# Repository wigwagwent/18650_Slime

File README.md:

# slimevr_pcb
A PCB design the size of a 18650 battery that supports the BMI160 designed for SlimeVR full-body trackers

- [18650_Slime-Main](/hardware/18650_Slime_main/) - A fully custom PCB that handles the IMU.

  Unlike most of the SlimeVR community, it uses the ESP32-C3, a newer and more
  powerful chip. Designed to be a more powerful development platform, as it natively
  supports JTAG debugging over USB, more compilers and languages, including Rust,
  and supports Bluetooth LE v5.0.

- [18650_Slime-Battery](/hardware/18650_Slime_battery/) - Combines fast charging with protection

  It can be used with other boards that want an 18650 cell with a built in charge controller.

## License
**This hardware is licensed under the CERN-OHL-P v2 license**, which is a permissive,
non-viral and non-reciprocal open hardware license. Unlike software licenses like
MIT and Apache 2.0, it better handles the nuances of hardware and protects both
the licensor and licensee from patent lawsuits.

**Unless you explicitly state otherwise, any contribution intentionally submitted
for inclusion in this work by you, shall be licensed as above, without any
additional terms or conditions.**

### Conveying notice of License
Note that as part of the CERN-OHL-P v2 license, recipients of manufactured
hardware must also receive notice of the above license. One such
method of conveying the notice is to include a link to the original source repo,
or printing "Licensed under CERN-OHL-P v2" on the PCB silkscreen. For more info,
see [here](https://ohwr.org/project/cernohl/wikis/uploads/8a6b5d01f71c207c49493e4d114d61e6/cern_ohl_p_v2_howto.pdf).

This is conceptually similar to the MIT/Apache 2.0 Licenses, where the original
license must still be included as a notice even when the source is modified and
subsequently relicensed under different terms.

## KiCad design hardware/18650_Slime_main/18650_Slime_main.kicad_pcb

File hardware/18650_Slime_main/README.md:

# 18650 SlimeVR
This PCB is designed to be about the same size as a 18650 cell once fully assembled
and stacked. This is a stacked board design but in theory, all the hardware should
be able to fit onto one board but is separated to two boards.

## Useful Information
- IMU: BMI160 Module
- ESP32-C3 main processor

## Renders

## Changelog
A description of the changes in each revision can be found [here](CHANGELOG.md).

## Credits
The schematic was based on version 3.0 of the .
Big thanks to TheButlah for all the work he put into this schematic and into slimevr.
Also big thanks to Mosaic-Industries for there push button 
Final thanks to this github project that implements a usefull  for jlcpcb

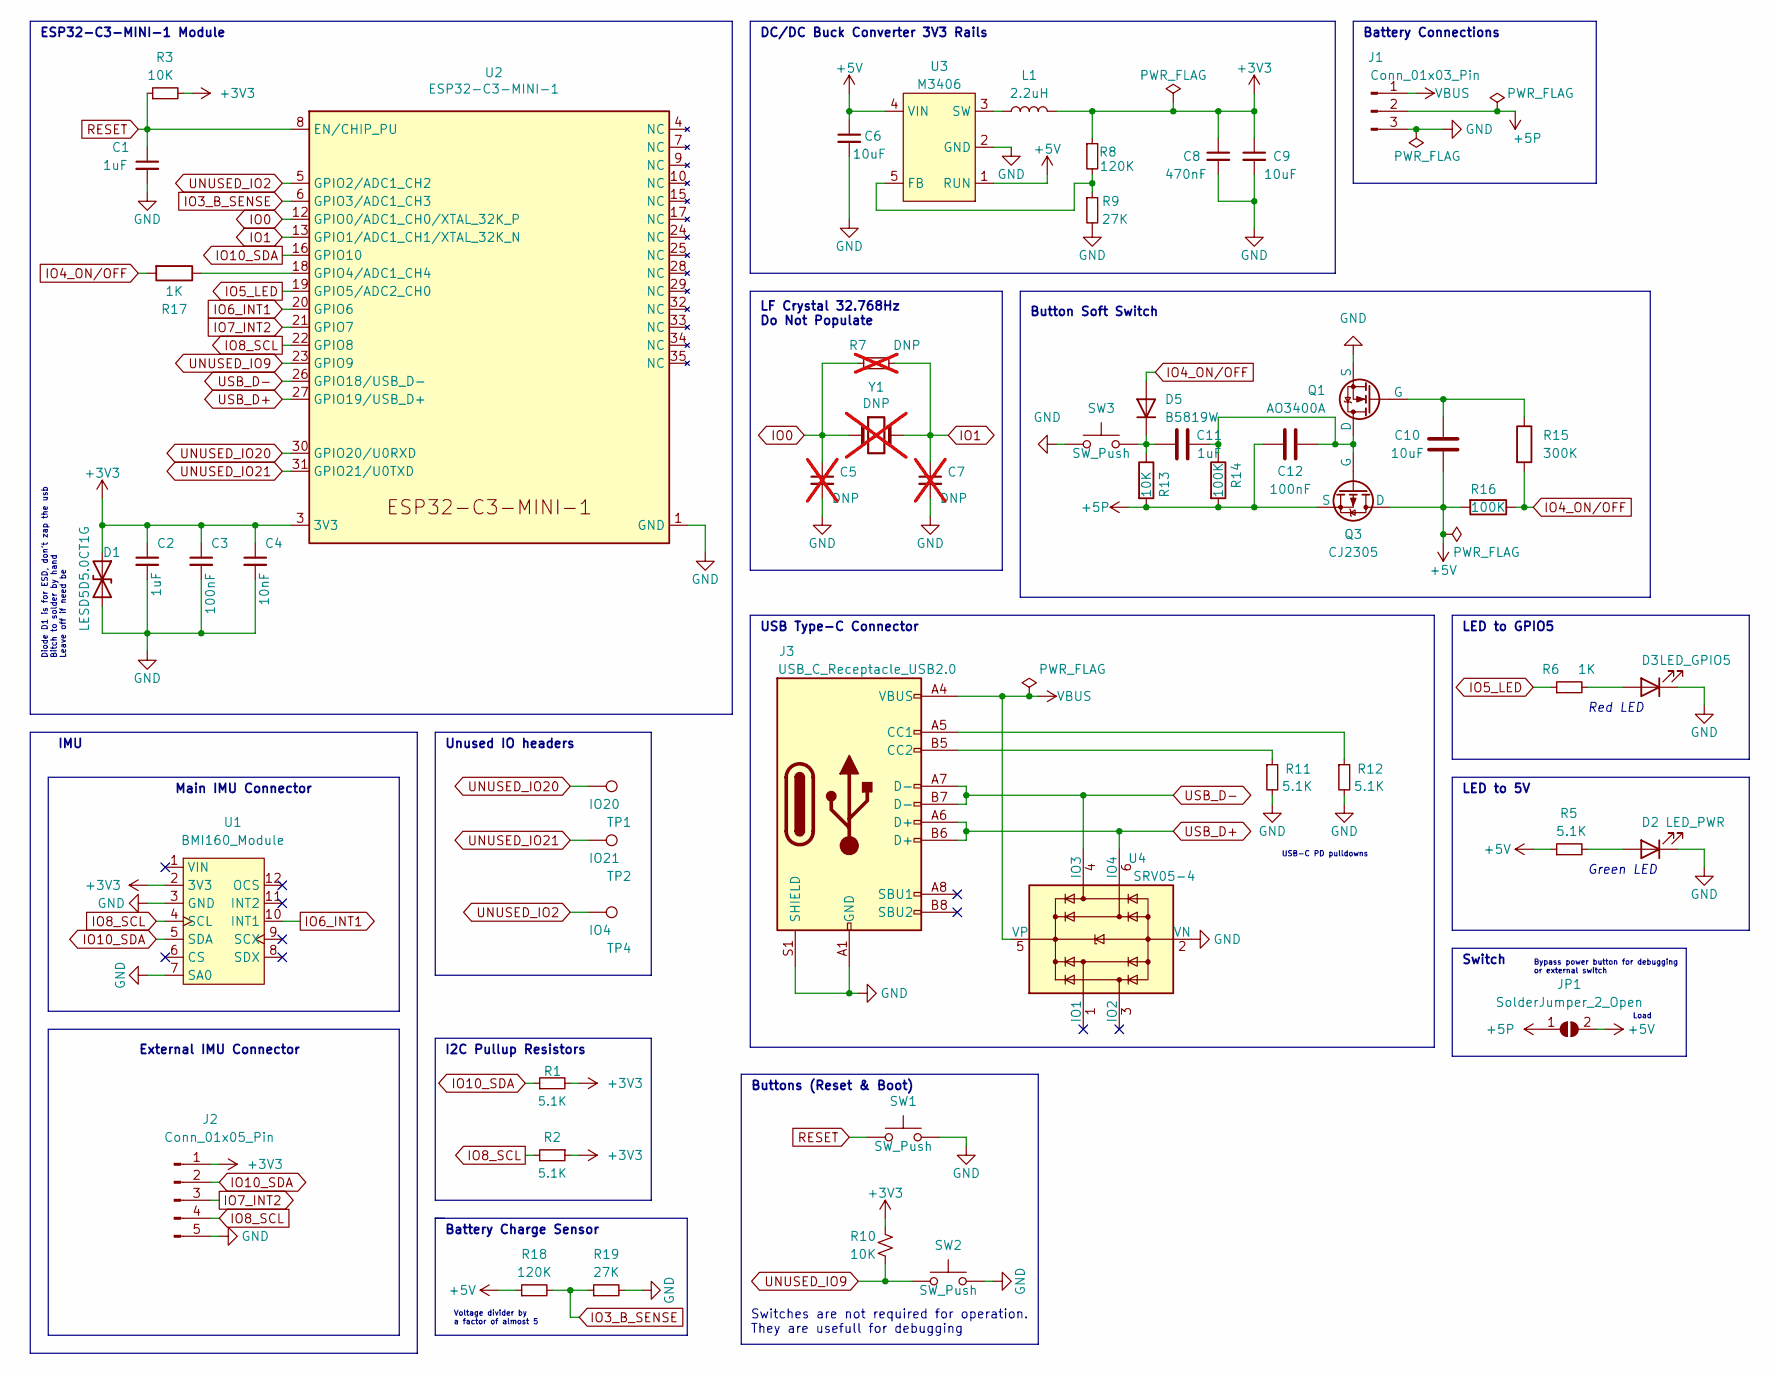
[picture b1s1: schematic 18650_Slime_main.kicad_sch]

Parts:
C1, C2, C11: 1uF; C_0805_2012Metric_Pad1.18x1.45mm_HandSolder; LCSC C28323
C3, C12: 100nF; C_0805_2012Metric_Pad1.18x1.45mm_HandSolder; LCSC C49678
C4: 10nF; C_0805_2012Metric_Pad1.18x1.45mm_HandSolder; LCSC C1710
C5, C7: DNP; C_0603_1608Metric; LCSC DNP; not fitted
C6, C9, C10: 10uF; C_0805_2012Metric_Pad1.18x1.45mm_HandSolder; LCSC C15850
C8: 470nF; C_0805_2012Metric_Pad1.18x1.45mm_HandSolder; LCSC C13967
D1: LESD5D5.0CT1G; D_SOD-523; LCSC C5199850
D2: LED_PWR; D_0805_2012Metric_Pad1.15x1.40mm_HandSolder; LCSC C688883
D3: LED_GPIO5; D_0805_2012Metric_Pad1.15x1.40mm_HandSolder; LCSC C84256
D5: B5819W; D_SOD-123; LCSC C8598
J1: Conn_01x03_Pin; PinHeader_1x03_P2.54mm_Horizontal; LCSC DNP
J2: Conn_01x05_Pin; PinHeader_1x05_P2.00mm_Vertical; LCSC DNP
J3: USB_C_Receptacle_USB2.0; USB_C_Receptacle_XKB_U262-16XN-4BVC11; LCSC C319148
JP1: SolderJumper_2_Open; SolderJumper-2_P1.3mm_Open_TrianglePad1.0x1.5mm; LCSC DNP
L1: 2.2uH; SMMS0420; LCSC C133191
Q1: AO3400A; SOT-23; LCSC C347475
Q3: CJ2305; SOT-23; LCSC C8549
R1, R2, R5, R11, R12: 5.1K; R_0805_2012Metric_Pad1.20x1.40mm_HandSolder; LCSC C27834
R3, R10, R13: 10K; R_0805_2012Metric_Pad1.20x1.40mm_HandSolder; LCSC C17414
R6, R17: 1K; R_0805_2012Metric_Pad1.20x1.40mm_HandSolder; LCSC C17513
R7: DNP; R_0603_1608Metric; LCSC DNP; not fitted
R8, R18: 120K; R_0805_2012Metric_Pad1.20x1.40mm_HandSolder; LCSC C17436
R9, R19: 27K; R_0805_2012Metric_Pad1.20x1.40mm_HandSolder; LCSC C17593
R14, R16: 100K; R_0805_2012Metric_Pad1.20x1.40mm_HandSolder; LCSC C149504
R15: 300K; R_0805_2012Metric_Pad1.20x1.40mm_HandSolder; LCSC C17616
SW1, SW2, SW3: SW_Push; TSC005A1732A; LCSC C2888878
TP1: IO20; TestPoint_Pad_D1.0mm; LCSC DNP
TP2: IO21; TestPoint_Pad_D1.0mm; LCSC DNP
TP4: IO4; TestPoint_Pad_D1.0mm; LCSC DNP
U1: BMI160_Module; BMI160; LCSC DNP
U2: ESP32-C3-MINI-1; ESP32-C3-MINI-1_HandSoldering; LCSC C2838502
U3: M3406; SOT-23-5_HandSoldering; LCSC C83224
U4: SRV05-4; SOT-23-6_Handsoldering; LCSC C558418
Y1: DNP; Crystal_SMD_3215-2Pin_3.2x1.5mm; LCSC DNP; not fitted

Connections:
+3V3: C2.1, C3.1, C4.1, C8.1, C9.1, D1.1 (A1), J2.1, L1.2, R1.2, R2.1, R3.2, R8.1, R10.1, U1.2 (3V3), U2.3 (3V3)
+5P: C12.1, J1.2, JP1.1 (A), Q3.3 (S), R13.2, R14.2
+5V: C6.1, C10.2, JP1.2 (B), Q3.1 (D), R5.1, R16.2, R18.1, U3.1 (RUN), U3.4 (VIN)
GND: C1.2, C2.2, C3.2, C4.2, C5.2, C6.2, C7.2, C8.2, C9.2, D1.2 (A2), D2.1 (K), D3.1 (K), J1.3, J2.5, J3.A1 (GND), J3.A12 (GND), J3.B1 (GND), J3.B12 (GND), J3.S1 (SHIELD), Q1.3 (S), R9.2, R11.2, R12.2, R19.2, SW1.2, SW2.2, SW3.1, U1.3 (GND), U1.7 (SA0), U2.1 (GND), U2.2 (GND), U2.11 (GND), U2.14 (GND), U2.36 (GND), U2.37 (GND), U2.38 (GND), U2.39 (GND), U2.40 (GND), U2.41 (GND), U2.42 (GND), U2.43 (GND), U2.44 (GND), U2.45 (GND), U2.46 (GND), U2.47 (GND), U2.48 (GND), U2.49 (GND), U2.50 (GND), U2.51 (GND), U2.52 (GND), U2.53 (GND), U3.2 (GND), U4.2 (VN)
IO0: C5.1, R7.1, U2.12 (GPIO0/ADC1_CH0/XTAL_32K_P), Y1.1
IO1: C7.1, R7.2, U2.13 (GPIO1/ADC1_CH1/XTAL_32K_N), Y1.2
IO3_B_SENSE: R18.2, R19.1, U2.6 (GPIO3/ADC1_CH3)
IO4_ON/OFF: D5.2 (A), R15.2, R16.1, R17.2
IO5_LED: R6.1, U2.19 (GPIO5/ADC2_CH0)
IO6_INT1: U1.10 (INT1), U2.20 (GPIO6)
IO7_INT2: J2.3, U2.21 (GPIO7)
IO8_SCL: J2.4, R2.2, U1.4 (SCL), U2.22 (GPIO8)
IO10_SDA: J2.2, R1.1, U1.5 (SDA), U2.16 (GPIO10)
unnamed: D2.2 (A), R5.2
unnamed: D3.2 (A), R6.2
unnamed: C11.2, D5.1 (K), R13.1, SW3.2
unnamed: J3.A5 (CC1), R12.1
unnamed: J3.B5 (CC2), R11.1
unnamed: C11.1, C12.2, Q1.1 (D), Q3.2 (G), R14.1
unnamed: C10.1, Q1.2 (G), R15.1
unnamed: R17.1, U2.18 (GPIO4/ADC1_CH4)
unnamed: R8.2, R9.1, U3.5 (FB)
unnamed: L1.1, U3.3 (SW)
RESET: C1.1, R3.1, SW1.1, U2.8 (EN/CHIP_PU)
UNUSED_IO2: TP4.1, U2.5 (GPIO2/ADC1_CH2)
UNUSED_IO9: R10.2, SW2.1, U2.23 (GPIO9)
UNUSED_IO20: TP1.1, U2.30 (GPIO20/U0RXD)
UNUSED_IO21: TP2.1, U2.31 (GPIO21/U0TXD)
USB_D+: J3.A6 (D+), J3.B6 (D+), U2.27 (GPIO19/USB_D+), U4.6 (IO4)
USB_D-: J3.A7 (D-), J3.B7 (D-), U2.26 (GPIO18/USB_D-), U4.4 (IO3)
VBUS: J1.1, J3.A4 (VBUS), J3.A9 (VBUS), J3.B4 (VBUS), J3.B9 (VBUS), U4.5 (VP)

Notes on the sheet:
LED to 5V
Load
I2C Pullup Resistors
Diode D1 is for ESD, don't zap the usb Bitch to solder by hand Leave off if need be
Voltage divider by a factor of almost 5
LF Crystal 32.768Hz Do Not Populate
External IMU Connector
USB-C PD pulldowns
IMU
DC/DC Buck Converter 3V3 Rails
Buttons (Reset & Boot)
Main IMU Connector
Battery Connections
Battery Charge Sensor
Bypass power button for debugging or external switch
Button Soft Switch
Unused IO headers
LED to GPIO5
Switches are not required for operation. They are usefull for debugging
ESP32-C3-MINI-1 Module
Green LED
USB Type-C Connector
Red LED
Switch

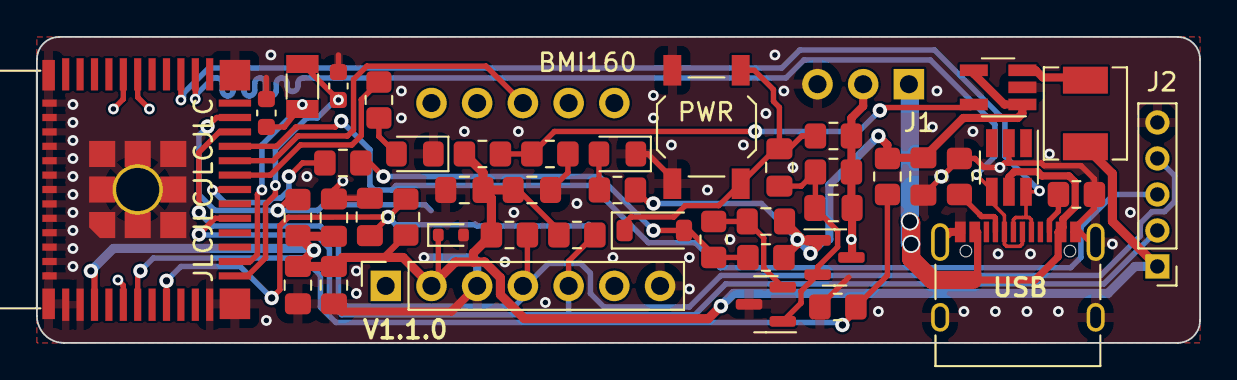
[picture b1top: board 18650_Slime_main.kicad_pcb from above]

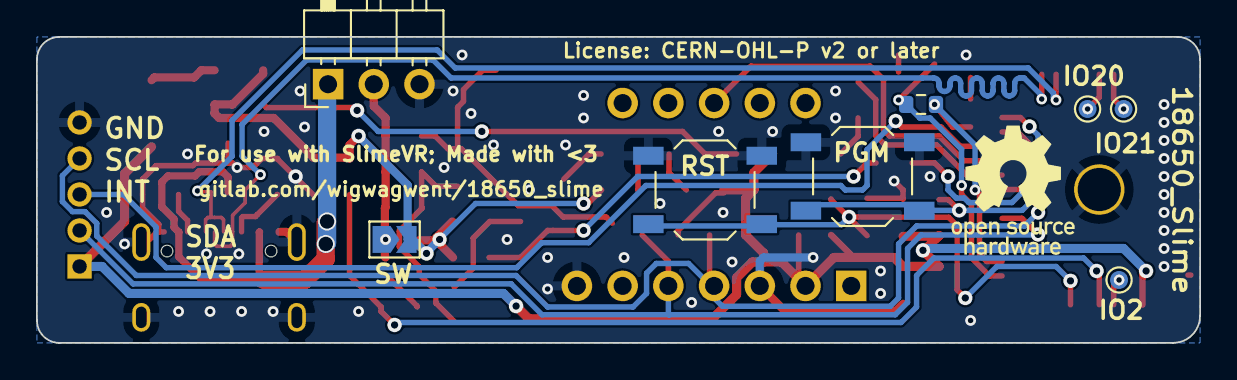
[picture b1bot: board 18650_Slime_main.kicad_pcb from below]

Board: 2 copper layers, 64.6 x 17.0 mm, 52 parts (8 on the bottom side), 31 nets.

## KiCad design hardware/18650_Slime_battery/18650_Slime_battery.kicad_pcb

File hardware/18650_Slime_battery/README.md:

# 18650 SlimeVR Battery
This PCB is designed to be about the same size as a 18650 cell and contains all the charging and protection
circuitry for that one cell. It has under/over voltage, over current through a 350mA resettable fuse, and short 
circuit protection. It supports charging rates up to 3A with the current setting being 2.1A.

## Renders

## Changelog
A description of the changes in each revision can be found [here](CHANGELOG.md).

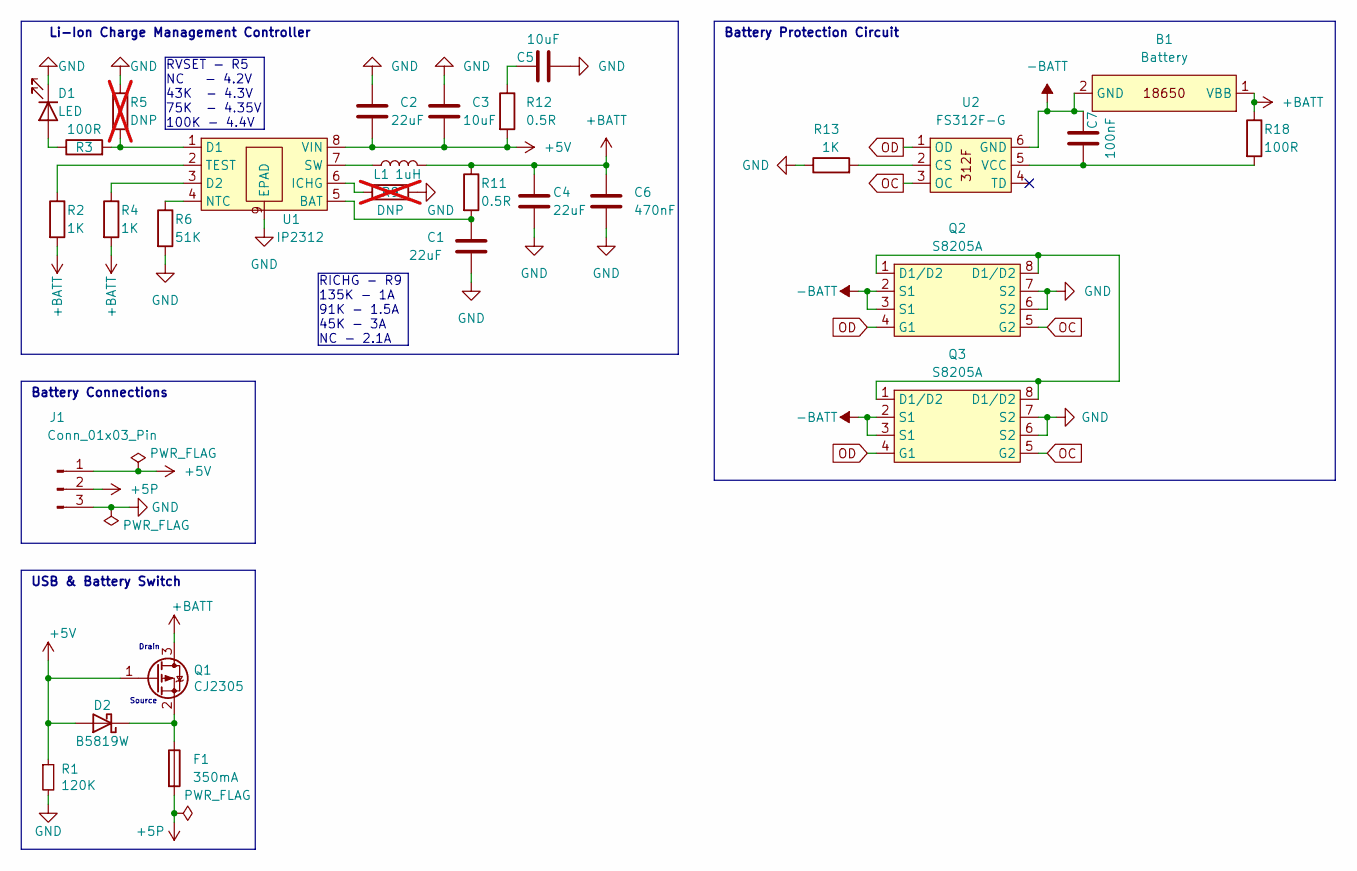
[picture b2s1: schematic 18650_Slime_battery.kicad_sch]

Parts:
B1: Battery; 18650_Battery; LCSC DNP
C1, C2, C4: 22uF; C_0805_2012Metric_Pad1.18x1.45mm_HandSolder; LCSC C45783
C3, C5: 10uF; C_0805_2012Metric_Pad1.18x1.45mm_HandSolder; LCSC C15850
C6: 470nF; C_0805_2012Metric_Pad1.18x1.45mm_HandSolder; LCSC C13967
C7: 100nF; C_0805_2012Metric_Pad1.18x1.45mm_HandSolder; LCSC C49678
D1: LED; LED_0805_2012Metric_Pad1.15x1.40mm_HandSolder; LCSC C84256
D2: B5819W; D_SOD-123; LCSC C8598
F1: 350mA; Fuse_0805_2012Metric_Pad1.15x1.40mm_HandSolder; LCSC C269103
J1: Conn_01x03_Pin; PinHeader_1x03_P2.54mm_Horizontal
L1: 1uH; SMMS0420; LCSC C133189
Q1: CJ2305; SOT-23; LCSC C8549
Q2, Q3: S8205A; TSSOP-8_4.4x3mm_P0.65mm; LCSC C436910
R1: 120K; R_0805_2012Metric_Pad1.20x1.40mm_HandSolder; LCSC C17436
R2, R4, R13: 1K; R_0805_2012Metric_Pad1.20x1.40mm_HandSolder; LCSC C17513
R3, R18: 100R; R_0805_2012Metric_Pad1.20x1.40mm_HandSolder; LCSC C17408
R5, R9: DNP; R_0805_2012Metric_Pad1.20x1.40mm_HandSolder; LCSC DNP; not fitted
R6: 51K; R_0805_2012Metric_Pad1.20x1.40mm_HandSolder; LCSC C17737
R11, R12: 0.5R; R_0805_2012Metric_Pad1.20x1.40mm_HandSolder; LCSC C327217
U1: IP2312; LCSC C605433
U2: FS312F-G; SOT-23-6_Handsoldering; LCSC C82736

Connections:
+5P: F1.2, J1.2
+5V: C2.2, C3.2, D2.2 (A), J1.1, Q1.1 (G), R1.1, R12.2, U1.8 (VIN)
+BATT: B1.1 (VBB), C4.1, C6.1, L1.2, Q1.3 (D), R2.2, R4.2, R11.1, R18.1
-BATT: B1.2 (GND), C7.2, Q2.2 (S1), Q2.3 (S1), Q3.2 (S1), Q3.3 (S1), U2.6 (GND)
GND: C1.2, C2.1, C3.1, C4.2, C5.1, C6.2, D1.1 (K), J1.3, Q2.6 (S2), Q2.7 (S2), Q3.6 (S2), Q3.7 (S2), R1.2, R5.1, R6.2, R9.2, R13.1, U1.9 (EPAD)
unnamed: C5.2, R12.1
unnamed: D1.2 (A), R3.1
unnamed: D2.1 (K), F1.1, Q1.2 (S)
unnamed: Q2.1 (D1/D2), Q2.8 (D1/D2), Q3.1 (D1/D2), Q3.8 (D1/D2)
unnamed: C1.1, R11.2, U1.5 (BAT)
unnamed: R3.2, R5.2, U1.1 (D1)
unnamed: R4.1, U1.3 (D2)
unnamed: R9.1, U1.6 (ICHG)
unnamed: R6.1, U1.4 (NTC)
unnamed: L1.1, U1.7 (SW)
unnamed: R2.1, U1.2 (TEST)
unnamed: R13.2, U2.2 (CS)
unnamed: C7.1, R18.2, U2.5 (VCC)
OC: Q2.5 (G2), Q3.5 (G2), U2.3 (OC)
OD: Q2.4 (G1), Q3.4 (G1), U2.1 (OD)

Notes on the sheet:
RICHG - R9 135K - 1A 91K - 1.5A 45K - 3A NC - 2.1A
Battery Connections
RVSET - R5 NC - 4.2V 43K - 4.3V 75K - 4.35V 100K - 4.4V
Battery Protection Circuit
Li-Ion Charge Management Controller
Drain
Source
USB & Battery Switch

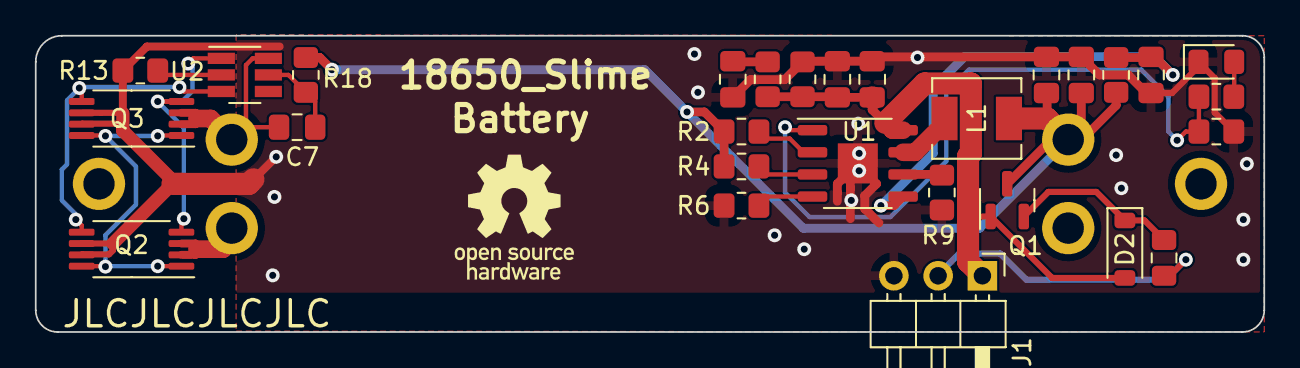
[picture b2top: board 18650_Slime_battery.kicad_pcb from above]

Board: 2 copper layers, 70.5 x 17.0 mm, 29 parts (1 on the bottom side), 20 nets.

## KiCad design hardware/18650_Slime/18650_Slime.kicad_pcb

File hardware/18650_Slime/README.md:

# 18650 SlimeVR
This PCB is designed to be about the same size as a 18650 cell once fully assembled
and stacked. This is a stacked board design but in theory, all the hardware should
be able to fit onto one board.

## Useful Information
- IMU: BMI160 with BMM150
- ESP32-C3 main processor

**Note:** BMM150 is not supported in slimevr yet.

## Renders

## Changelog
A description of the changes in each revision can be found [here](CHANGELOG.md).

## Credits
The schematic was based on version 3.0 of the .
Big thanks to @TheButlah for all the work he put into this schematic and into slimevr.

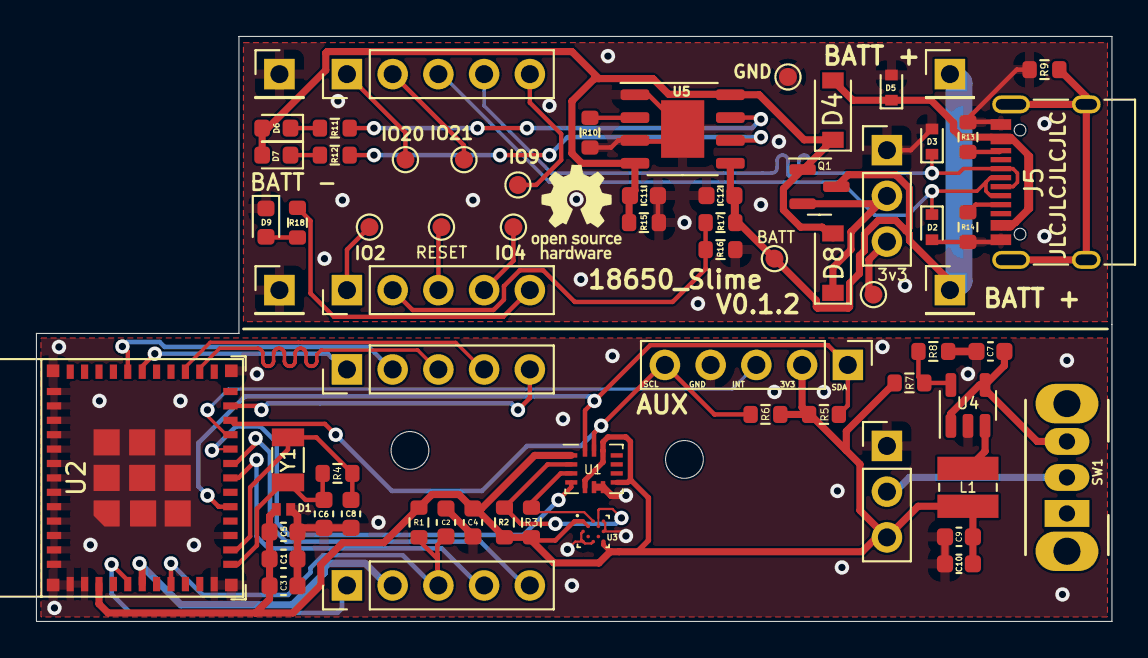
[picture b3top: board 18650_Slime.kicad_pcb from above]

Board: 2 copper layers, 59.8 x 32.5 mm, 71 parts (0 on the bottom side), 49 nets.

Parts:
C1, C2: 1uF 16V; C_0603_1608Metric
C3: 100nF 10V; C_0603_1608Metric
C4, C7: 4.7uF; C_0603_1608Metric
C5: 10nF 10V; C_0603_1608Metric
C6, C8: DNP; C_0603_1608Metric
C9: 470nF; C_0603_1608Metric
C10, C11, C12: 10uF; C_0603_1608Metric
D1: LESD8D3.3CAT5G; SOD882
D2, D3, D5: LESD5D5.0CT1G; D_SOD-523
D4, D8: B5819W; D_SOD-123
D6: CHRG; LED_0603_1608Metric
D7: FULL; LED_0603_1608Metric
D9: LED_IO5; LED_0603_1608Metric
H1, H1#2: MountingHole_2.1mm
J1: IMU_Connector; PinHeader_1x05_P2.54mm_Vertical
J2, J10: Conn_01x03_Male; PinHeader_1x03_P2.54mm_Vertical
J3, J4, J8, J9: Conn_01x05_Male; PinHeader_1x05_P2.54mm_Vertical
J5: USB_C_Receptacle_USB2.0; USB_C_Receptacle_XKB_U262-16XN-4BVC11
J6, J7: Batt +; PinHeader_1x01_P2.54mm_Vertical
J11, J12: Batt -; PinHeader_1x01_P2.54mm_Vertical
L1: 2.2uH; L_Wuerth_MAPI-3015
Q1: CJ2305; SOT-23
R1: 10kR 1%; R_0603_1608Metric
R2, R3, R5, R6: 4.7K; R_0603_1608Metric
R4: DNP; R_0603_1608Metric
R7, R16: 120K 1%; R_0603_1608Metric
R8: 27K 1%; R_0603_1608Metric
R9, R15: 120K; R_0603_1608Metric
R10: 2K; R_0603_1608Metric
R11, R12, R18: 1K; R_0603_1608Metric
R13, R14: 5k1R 1%; R_0603_1608Metric
R17: 30K 1%; R_0603_1608Metric
SW1: SW_PWR; SW_CuK_OS102011MA1QN1_SPDT_Angled
TP1: BATT; TestPoint_Pad_D1.0mm
TP2: 3v3; TestPoint_Pad_D1.0mm
TP3: RESET; TestPoint_Pad_D1.0mm
TP4: IO20; TestPoint_Pad_D1.0mm
TP5: IO21; TestPoint_Pad_D1.0mm
TP6: IO4; TestPoint_Pad_D1.0mm
TP7: IO2; TestPoint_Pad_D1.0mm
TP8: IO9; TestPoint_Pad_D1.0mm
TP9: GND; TestPoint_Pad_D1.0mm
U1: BMI160; Bosch_LGA-14_3x2.5mm_P0.5mm
U2: ESP32-C3-MINI-1
U3: BMM150; WLCSP-12_1.56x1.56mm_P0.4mm
U4: M3406; SOT-23-5
U5: TP4056; HTSOP-8-1EP_3.9x4.9mm_P1.27mm_EP2.4x3.2mm
Y1: 32.768Hz; Crystal_SMD_3215-2Pin_3.2x1.5mm

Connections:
+3V3: C1.1, C3.1, C4.2, C5.1, C9.1, C10.1, D1.1 (A1), J1.2, J2.3, L1.2, R1.1, R2.2, R3.1, R5.2, R6.1, R7.1, U1.1 (SDO), U1.5 (VDDIO), U1.8 (VDD), U1.12 (CSB), U2.3 (3V3), U3.A1 (PS), U3.B2 (VDDIO), U3.E5 (VDD)
+5P: J2.2, SW1.2 (B)
+5V: C7.1, SW1.3 (C), U4.1 (RUN), U4.4 (VIN)
+BATT: C12.1, J6.1, J7.1, Q1.3 (D), R16.1, TP1.1, U5.5 (BAT)
/Top Level/5V: D8.1 (K), J10.2, Q1.2 (S)
/Top Level/+3V3: J10.3, TP2.1
/Top Level/B_SENSE: J9.2, R16.2, R17.1
/Top Level/GND: C11.2, C12.2, D2.2 (A2), D3.2 (A2), D5.2 (A2), D9.1 (K), J5.A1 (GND), J5.A12 (GND), J5.B1 (GND), J5.B12 (GND), J10.1, J11.1, J12.1, R9.2, R10.1, R13.2, R14.2, R15.2, R17.2, TP9.1, U5.1 (TEMP), U5.3 (GND), U5.9 (EP)
/Top Level/IO5_LED: J9.5, R18.1
/Top Level/RESET: J9.3, TP3.1
/Top Level/UNUSED_IO2: J9.1, TP7.1
/Top Level/UNUSED_IO4: J9.4, TP6.1
/Top Level/UNUSED_IO9: J8.5, TP8.1
/Top Level/UNUSED_IO20: J8.1, TP4.1
/Top Level/UNUSED_IO21: J8.2, TP5.1
/Top Level/USB_D+: D3.1 (A1), J5.A6 (D+), J5.B6 (D+), J8.4
/Top Level/USB_D-: D2.1 (A1), J5.A7 (D-), J5.B7 (D-), J8.3
B_SENSE: J3.2, U2.6 (GPIO3/ADC1_CH3)
GND: C1.2, C2.2, C3.2, C4.1, C5.2, C6.2, C7.2, C8.2, C9.2, C10.2, D1.2 (A2), J1.4, J2.1, R8.2, U1.6 (GNDIO), U1.7 (GND), U2.1 (GND), U2.2 (GND), U2.11 (GND), U2.14 (GND), U2.36 (GND), U3.A5 (CSB), U3.C1 (SDO), U3.C5 (GND), U3.E1 (GND), U3.E3 (GND), U4.2 (GND)
IO0: C6.1, R4.1, U2.12 (GPIO0/ADC1_CH0/XTAL_32K_P), Y1.1
IO1: C8.1, R4.2, U2.13 (GPIO1/ADC1_CH1/XTAL_32K_N), Y1.2
IO5_LED: J3.5, U2.19 (GPIO5/ADC2_CH0)
IO6_INT1: U1.4 (INT1), U2.20 (GPIO6)
IO7_INT2: J1.3, U2.21 (GPIO7)
IO8_SCL: J1.5, R6.2, U1.13 (SCx), U2.22 (GPIO8)
IO10_SDA: J1.1, R5.1, U1.14 (SDx), U2.16 (GPIO10)
unnamed: D4.2 (A), D5.1 (A1), J5.A4 (VBUS), J5.A9 (VBUS), J5.B4 (VBUS), J5.B9 (VBUS)
unnamed: D6.1 (K), R11.2
unnamed: D7.1 (K), R12.2
unnamed: D9.2 (A), R18.2
unnamed: J5.A5 (CC1), R14.1
unnamed: J5.B5 (CC2), R13.1
unnamed: J5.S1 (SHIELD), R9.1
unnamed: L1.1, U4.3 (SW)
unnamed: R2.1, U1.2 (ASDx), U3.B4 (SDI)
unnamed: R3.2, U1.3 (ASCx), U3.A3 (SCK)
unnamed: R7.2, R8.1, U4.5 (FB)
unnamed: R10.2, U5.2 (PROG)
unnamed: R11.1, U5.7 (CHRG)
unnamed: R12.1, U5.6 (STDBY)
RESET: C2.1, J3.3, R1.2, U2.8 (EN/CHIP_PU)
UNUSED_IO2: J3.1, U2.5 (GPIO2/ADC1_CH2)
UNUSED_IO4: J3.4, U2.18 (GPIO4/ADC1_CH4)
UNUSED_IO9: J4.5, U2.23 (GPIO9)
UNUSED_IO20: J4.1, U2.30 (GPIO20/U0RXD)
UNUSED_IO21: J4.2, U2.31 (GPIO21/U0TXD)
USB_D+: J4.4, U2.27 (GPIO19/USB_D+)
USB_D-: J4.3, U2.26 (GPIO18/USB_D-)
VBUS: C11.1, D4.1 (K), D6.2 (A), D7.2 (A), D8.2 (A), Q1.1 (G), R15.1, U5.4 (VCC), U5.8 (CE)

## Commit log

2022-12-07 Inital Commit
2022-12-07 Update to V0.1.1 of 18650_Slime
2022-12-07 Fixed Readme referencing wrong person
2022-12-08 v0.1.2 of 18650_slime
2023-06-18 inital design for next major version
2023-06-18 V1.0.0 of the battery module done
2023-07-06 V1.0.0 Release, UNTESTED
2023-07-07 Minor Changes INTESTING

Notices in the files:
hardware/18650_Slime/18650_Slime.kicad_pcb:
Licensed under CERN-OHL-P v2 or later
License: CERN-OHL-P v2 or later
